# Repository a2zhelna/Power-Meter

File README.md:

# Power-Meter Rundown

### Anthony Zhelnakov

Demo video: https://www.dropbox.com/s/2afd6wcfme4bhvw/PowerMeterDemo.mp4?dl=0

This is a DC power meter, which utilizes an ESP32 to host an access point, which a user on a browser can connect to and view real-time data from. It utilizes FreeRTOS to make use of the ESP32’s dual core architecture for reading and uploading data in parallel.

The inner 16-bit ADC chip (ADS8331), responsible for making all of the measurements, is capable of making 500k samples per second, but for the graphical data-visualisation method I am using and simplicity of the program, I found that maxing out at about 1k samples per second worked and looked just fine (the task scheduler of the ESP32 runs 1000 times a second, so I corresponded it to that).

This device was inteded to be used for analyzing realtime changes in power consumption: the user can analyze what happens during power-on/off cycles, sleep modes, different hardware modes, what happens when certain peripherals are turned on and off, which is all very helpful for diagnosing issues or just testing.

---

### Sockets:

**PS+:**
The power supply’s — which powers the unit — positive terminal’s voltage. The recommended maximum with reference to PS- is 23V. 

**PS-:**
The power supply’s negative terminal’s voltage (GND).

**Unit+:**
The positive supply terminal of the load / unit being tested.

**High Current In:**
The negative supply terminal of the load / unit being tested, IF it draws from 0 - 7.5A.

**Low Current In:**
The negative supply terminal of the load / unit being tested, IF it draws from 0 - 20mA (uses a 250mA fuse).3

---

### Instructions:

1. Connect power supply to PS+ and PS-, and connect the unit under test to UNIT+ and an appropriate CURRENT IN socket.
2. Turn on the power meter device.
3. Connect via Wi-Fi to the ESP32’s access point “Power Meter”. Password is “password”. 
4. Go to “192.168.77.77” in a browser.
5. You should be directed to the website. If the readings are nonsensically high or aren’t updating, turn off the device and go back to step 2!
6. Click the start button before considering any of the readings.
7. Turn on the power supply and unit that is being tested.
8. Measure POWER!!!
9. If the current surpasses 7.5A, the unit will be disconnected, and the reset/start button will need to be pressed again.

---

### Protection:

If the current through the HIGH input exceeds 7.5A, a relay disconnects the input from the current measurement circuit and in turn from GND. This current threshold can be adjusted with the potentiometer. Also, if the µC somehow detects this excessive current, a warning is shown on the website.

The LOW current input is protected with a 250mA fuse. Additionally, if the current exceeds 20mA through the low current input, then a warning is shown on the website. The reason being is because at higher currents, the ammeter circuit acts unpredictably and gives garbage results that shouldn’t be interpreted. If there’s a warning, it is recommended to restart the measurement, preferably with the higher current range. 
Note that this overcurrent notification method isn’t full proof, since it relies on the sampling rate of the device. If the current goes from <20mA to >20mA within the current re-sampling time, then the device will determine if there’s an overcurrent with garbage data, and possibly not display the warning.

One of the ADC inputs is connected to the HIGH current input to measure burden voltage. If this input gets connected to a large voltage, there’s a resistor and a clamping diode set up to prevent the ADC’s input from going above 5.1V. Due to the burden voltage always being below 1V, this doesn’t add any significant inaccuracies. 

---

### ADC inputs:

**Power supply voltage:**
Measures the voltage across PS+ and PS-. This is done through a voltage divider, which divides the input by 6. Due to the ADC having a reference voltage of 4.096V, the maximum input that can be measured is (4.096V x 6) = 24.576V. The absolute maximum input is (5.3V x 6) = 31.8V.

**High current measurement:**
Meant for measuring current going INTO the “High Current In” socket. This current goes through the L18P003D15 9A hall effect current sensor, who’s output also goes to a voltage divider which divides it by 3, for ADC safety.

**Low current measurement:**
Meant for measuring current going INTO the “Low Current In” socket. This current goes through an op amp circuit called a “feedback ammeter”, which itself has virtually no burden voltage. It is only effective for currents less than 20mA. The output goes directly to the ADC input.

**Offset/burden voltage:** 
Measures the voltage at the “High Current In” socket. This socket connects to an 8A power relay (used for protection), which routes the current through the hall effect current sensor, which then routes the current directly to the power supply’s ground (PS- socket). This configuration results in a ~100mOhm load. For higher currents, that results in a significant burden.
This measured burden voltage is then subtracted from the measured power supply voltage.
Note: This reveals a minor design flaw. The low current measurement circuit’s burden voltage (which mainly results from the fuse) is not measured. Though, it is almost insignificant.

---

### “Instantaneous Power”

The PS voltage, low-current, high-current, and offset/burden voltage measurements (which are utilized together to calculate “instantaneous” power) are each ~55us apart, respectively (5us PGA delay + 40us other delay).

---

### Power Supply

This device has its own power supply which connects to the main 115VAC outlet. Utilizing a transformer, linear regulators and buck converter, it provides 5V and 3.3V for digital circuits, and a separate 5V, -5Va, 15Va and -15Va for analog circuits. The main reason for this is to have access to low-noise analog supply voltages, so that the output of the hall effect current sensor is clean and the ADC makes measurements as accurately as possible.

Both the power supply and the power meter PCBs utilize inductors to minimize noise on the analog line due to the digital line. The ESP32 µC sometimes requires a lot of current (upwards of 240mA), and supplying this using a linear regulator is not efficient and requires a large heatsink + constant airflow. I instead used a buck converter for this purpose, who’s output produces noise on the digital line which is “filtered” by these inductors.

---

### Accuracy

The power meter device was compared to (and calibrated with) the FLUKE 77IV Multimeter. The measurements/readings from the power supply (PS) are also listed below.

To summarize, there’s virtually always a <1% magnitude deviation from the FLUKE measurements with low current above 3mA, high current above 100mA, and voltage measurements above 300mV. See tables below for exact comparisons.

> Current at 20mA range setting

> Current at 7.5A range setting

> Voltage (No Load)

> Voltage (at UNIT+ and HIGH CURRENT IN sockets) with 1Ohm Load

---

### Voltage Burden

For the low current measurement circuit, the highest possible voltage drop across it is insignificant, due to the low current it's meant for.

For the high current measurement circuit however, there’s about 100mOhms from the overcurrent relay and hall effect sensor, and there’s about 45mOhms from the wires connecting the unit’s sockets to the actual power meter PCB. To give an idea on the effect this has, at 7.5A, it results in a ~1V drop across those elements. 
The ADC actually measures the burden across the relay and hall effect, but as for the wires’ burden, an estimation is calculated. These voltages are then subtracted from the measured power supply voltage to give the voltage across the sockets that the unit connects to. On top of that, there’s an option to specify resistance of the leads that connect to the unit. Using the measured current, more voltage burden is calculated and subtracted from the power supply voltage 

**It is thus imperative** for the user to look at the voltage displayed on the website to make evaluations on the unit’s power consumption, instead of using the value displayed on their power supply. 
(But the user must be careful with the custom lead resistance option as entering a high resistance will significantly drop the voltage shown on the website, providing the user with a skewed view on how much they can increase the power supply voltage — which can lead to the ADC being damaged). 

Burden voltage is also the justification for the recommended 23V PS input limit. As an example, let's say the user’s unit under test is drawing 7.5A of current. This means that the voltage across the mentioned-before elements of the measurement device is around 1V. Thus, the voltage across the unit is 1V less than the voltage from the PS. If the user applies the maximum measurable voltage, 24.5V, at the PS inputs, then the website will display 23.5V. If the user knows they can measure up to 24.5V, they might think they can increase the PS voltage after it has already oversaturated the ADC input, which will lend inaccurate results. 
So, for the device to be reliable in this edge case, it is recommended to apply a maximum voltage of 23V at the unit’s terminals.

---

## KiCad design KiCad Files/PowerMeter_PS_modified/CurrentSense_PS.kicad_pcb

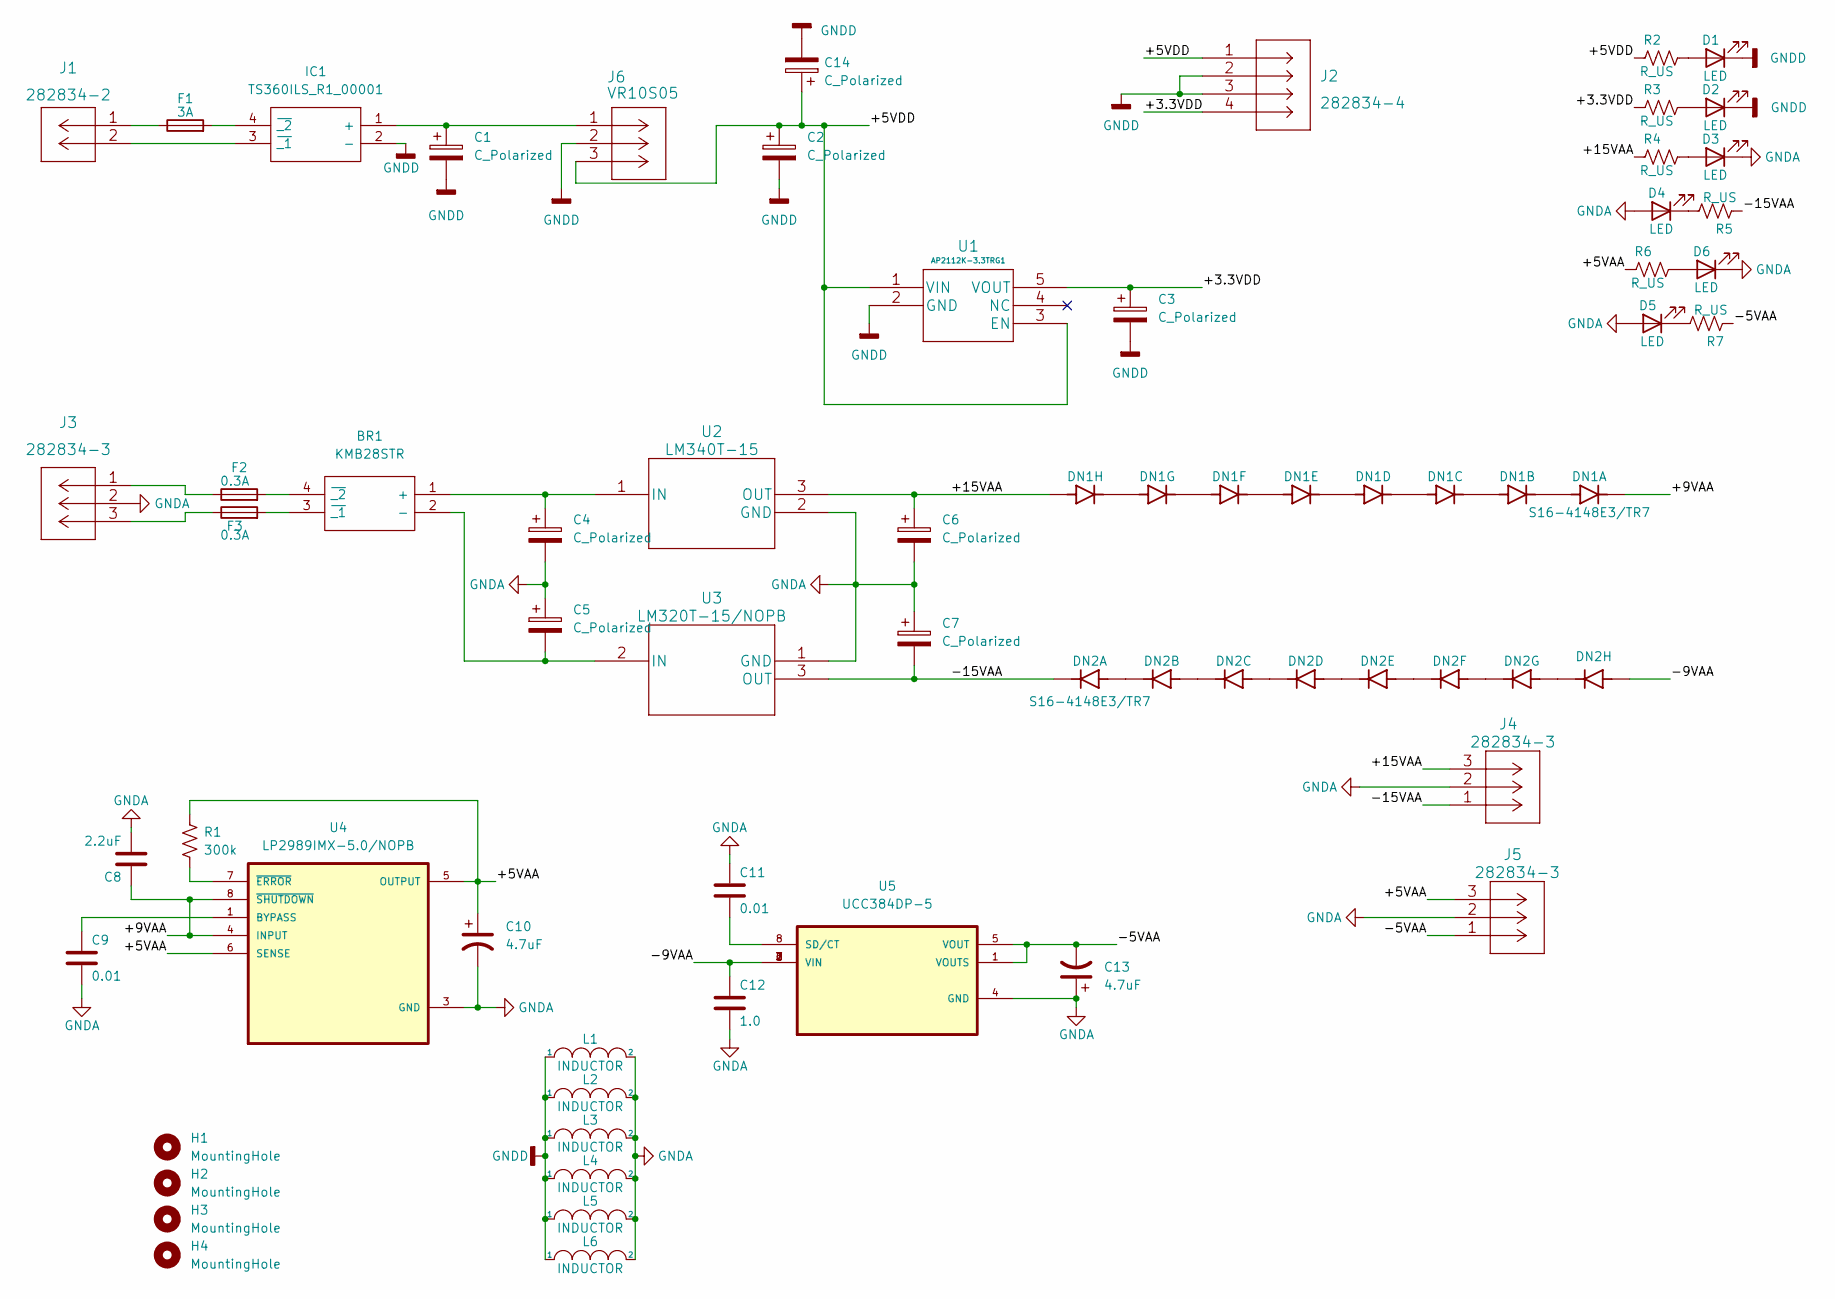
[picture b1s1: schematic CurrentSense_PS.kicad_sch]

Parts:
BR1: KMB28STR; SOP250P700X290-4N; Manufacturer_Part_Number KMB28STR
C1, C2, C3, C4, C5, C6, C7, C14: C_Polarized; CP_Radial_D5.0mm_P2.50mm
C8: 2.2uF; C_0805_2012Metric
C9, C11: 0.01; C_0603_1608Metric
C10, C13: 4.7uF; CP_EIA-7343-15_Kemet-W
C12: 1.0; C_0603_1608Metric
D1, D2, D3, D4, D5, D6: LED; LED_0603_1608Metric
DN1, DN2: S16-4148E3/TR7; SOIC127P599X195-16N; PARTREV G
F1: 3A; Fuse_1206_3216Metric
F2, F3: 0.3A; Fuse_1206_3216Metric
H1, H2, H3, H4: MountingHole; MountingHole_3.2mm_M3
IC1: TS360ILS_R1_00001; SOP400P650X145-4N; Mouser Part Number 241-TS360ILSR100001
J1: 282834-2
J2: 282834-4
J3, J4, J5: 282834-3
J6: VR10S05
L1, L2, L3, L4, L5, L6: INDUCTOR; L_1206_3216Metric
R1: 300k; R_0603_1608Metric
R2, R3, R4, R5, R6, R7: R_US; R_0603_1608Metric
U1: AP2112K-3.3TRG1
U2: LM340T-15
U3: LM320T-15/NOPB; LM320T-15&slash_NOPB
U4: LP2989IMX-5.0/NOPB; SOIC127P599X175-8N
U5: UCC384DP-5; SOIC127P599X175-8N

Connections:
/+3.3VDD: C3.1, J2.4, R3.1, U1.5 (VOUT)
/+5VAA: C10.1, J5.3, R1.1, R6.1, U4.5 (OUTPUT), U4.6 (SENSE)
/+5VDD: C2.1, C14.1, J2.1, J6.3, R2.1, U1.1 (VIN), U1.3 (EN)
/+9VAA: C8.1, DN1.1, U4.4 (INPUT), U4.8 (~SHUTDOWN)
/+15VAA: C6.1, DN1.9, J4.3, R4.1, U2.3 (OUT)
/-5VAA: C13.2, J5.1, R7.1, U5.1 (VOUTS), U5.5 (VOUT)
/-9VAA: C12.1, DN2.9, U5.2 (VIN), U5.3 (VIN), U5.6 (VIN), U5.7 (VIN)
/-15VAA: C7.2, DN2.1, J4.1, R5.1, U3.3 (OUT)
GNDA: C4.2, C5.1, C6.2, C7.1, C8.2, C9.2, C10.2, C11.1, C12.2, C13.1, D3.1 (K), D4.2 (A), D5.2 (A), D6.1 (K), J3.2, J4.2, J5.2, L1.2, L2.2, L3.2, L4.2, L5.2, L6.2, U2.2 (GND), U3.1 (GND), U4.3 (GND), U5.4 (GND)
GNDD: C1.2, C2.2, C3.2, C14.2, D1.1 (K), D2.1 (K), IC1.2 (-), J2.2, J2.3, J6.2, L1.1, L2.1, L3.1, L4.1, L5.1, L6.1, U1.2 (GND)
unnamed: BR1.1 (+), C4.1, U2.1 (IN)
unnamed: BR1.2 (-), C5.2, U3.2 (IN)
unnamed: BR1.3 (~_1), F3.2
unnamed: BR1.4 (~_2), F2.2
unnamed: C1.1, IC1.1 (+), J6.1
unnamed: C9.1, U4.1 (BYPASS)
unnamed: C11.2, U5.8 (SD/CT)
unnamed: D1.2 (A), R2.2
unnamed: D2.2 (A), R3.2
unnamed: D3.2 (A), R4.2
unnamed: D4.1 (K), R5.2
unnamed: D5.1 (K), R7.2
unnamed: D6.2 (A), R6.2
unnamed: DN1.8, DN1.10
unnamed: DN1.7, DN1.11
unnamed: DN1.6, DN1.12
unnamed: DN1.5, DN1.13
unnamed: DN1.4, DN1.14
unnamed: DN1.3, DN1.15
unnamed: DN1.2, DN1.16
unnamed: DN2.8, DN2.10
unnamed: DN2.7, DN2.11
unnamed: DN2.6, DN2.12
unnamed: DN2.5, DN2.13
unnamed: DN2.4, DN2.14
unnamed: DN2.3, DN2.15
unnamed: DN2.2, DN2.16
unnamed: F1.1, J1.1
unnamed: F1.2, IC1.4 (~_2)
unnamed: F2.1, J3.1
unnamed: F3.1, J3.3
unnamed: IC1.3 (~_1), J1.2
unnamed: R1.2, U4.7 (~ERROR)

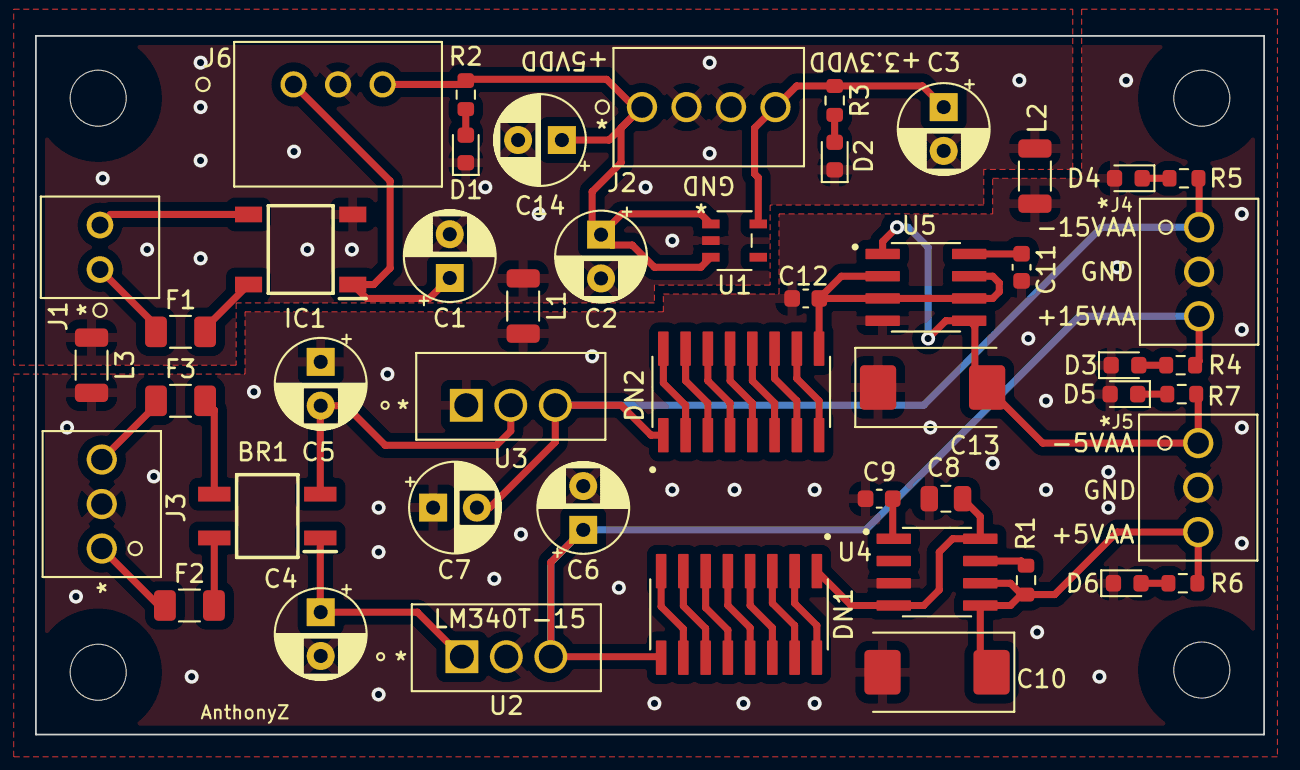
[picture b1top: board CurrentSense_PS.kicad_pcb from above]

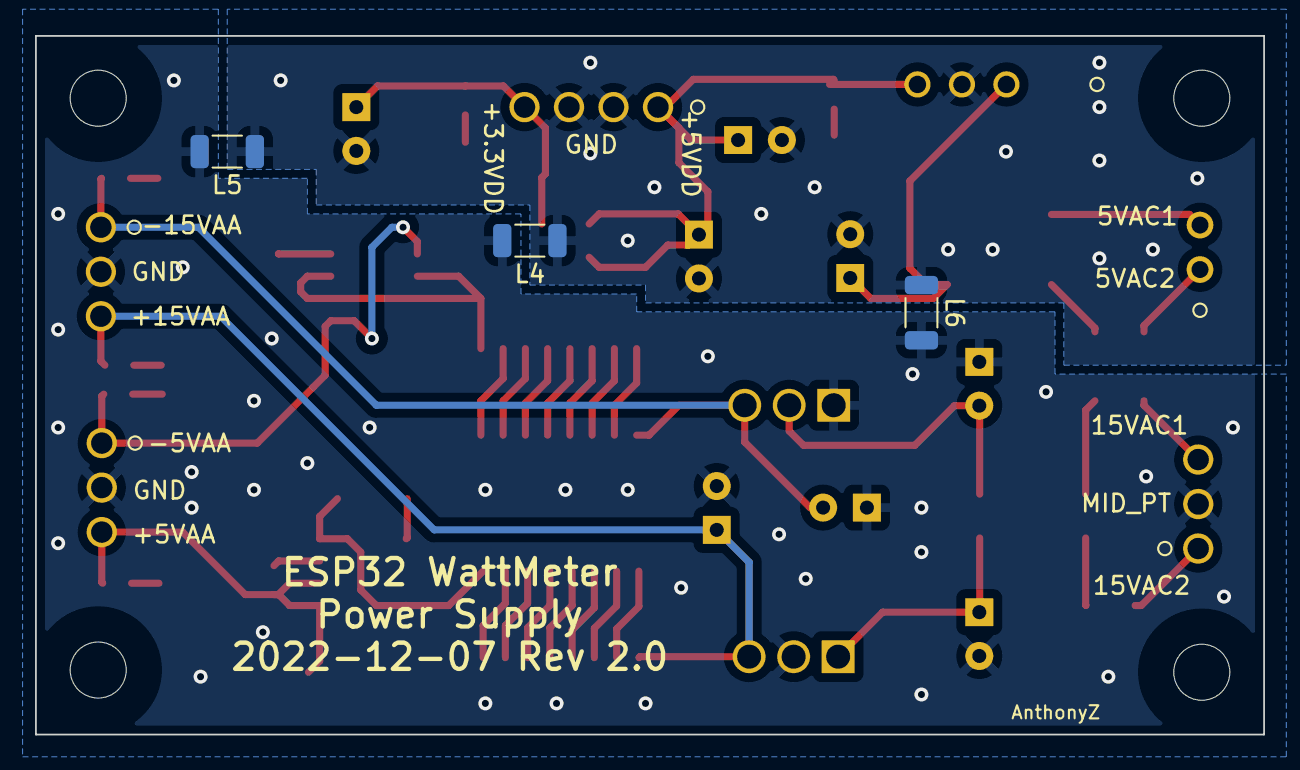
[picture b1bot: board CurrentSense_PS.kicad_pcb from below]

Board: 2 copper layers, 70.1 x 39.9 mm, 55 parts (3 on the bottom side), 43 nets.

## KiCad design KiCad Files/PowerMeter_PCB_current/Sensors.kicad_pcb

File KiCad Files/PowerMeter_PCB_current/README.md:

# Voltage-Current-Sense-Circuit

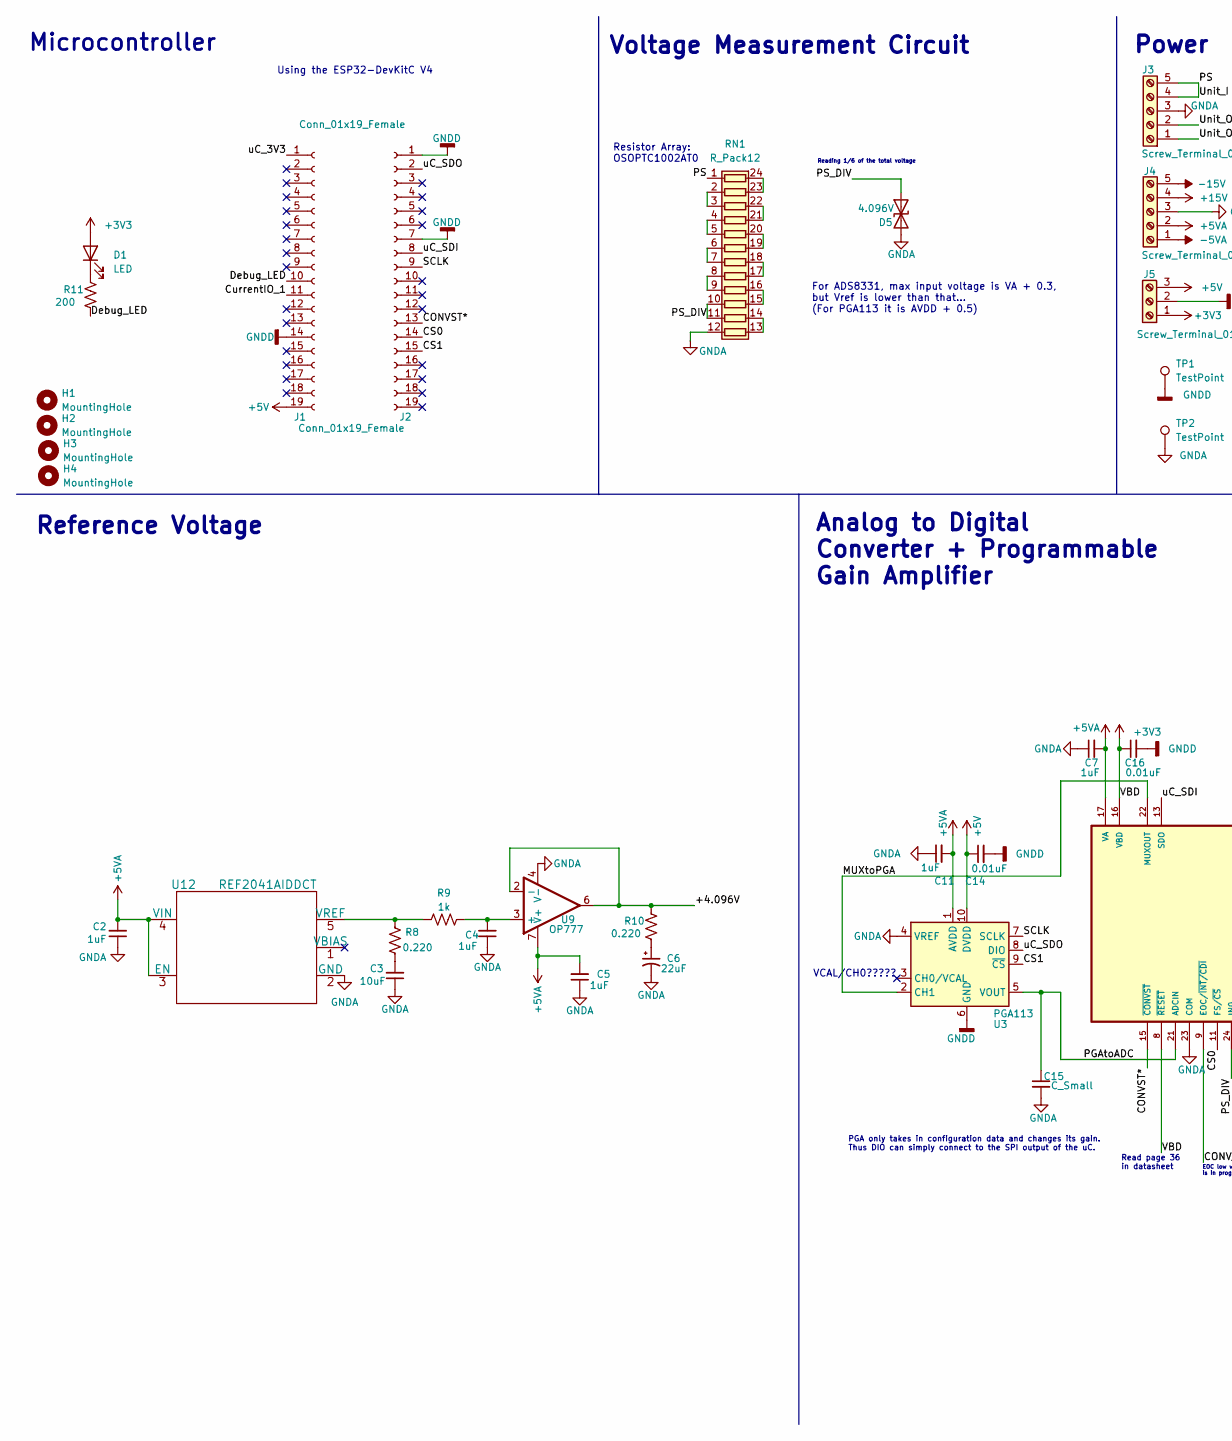
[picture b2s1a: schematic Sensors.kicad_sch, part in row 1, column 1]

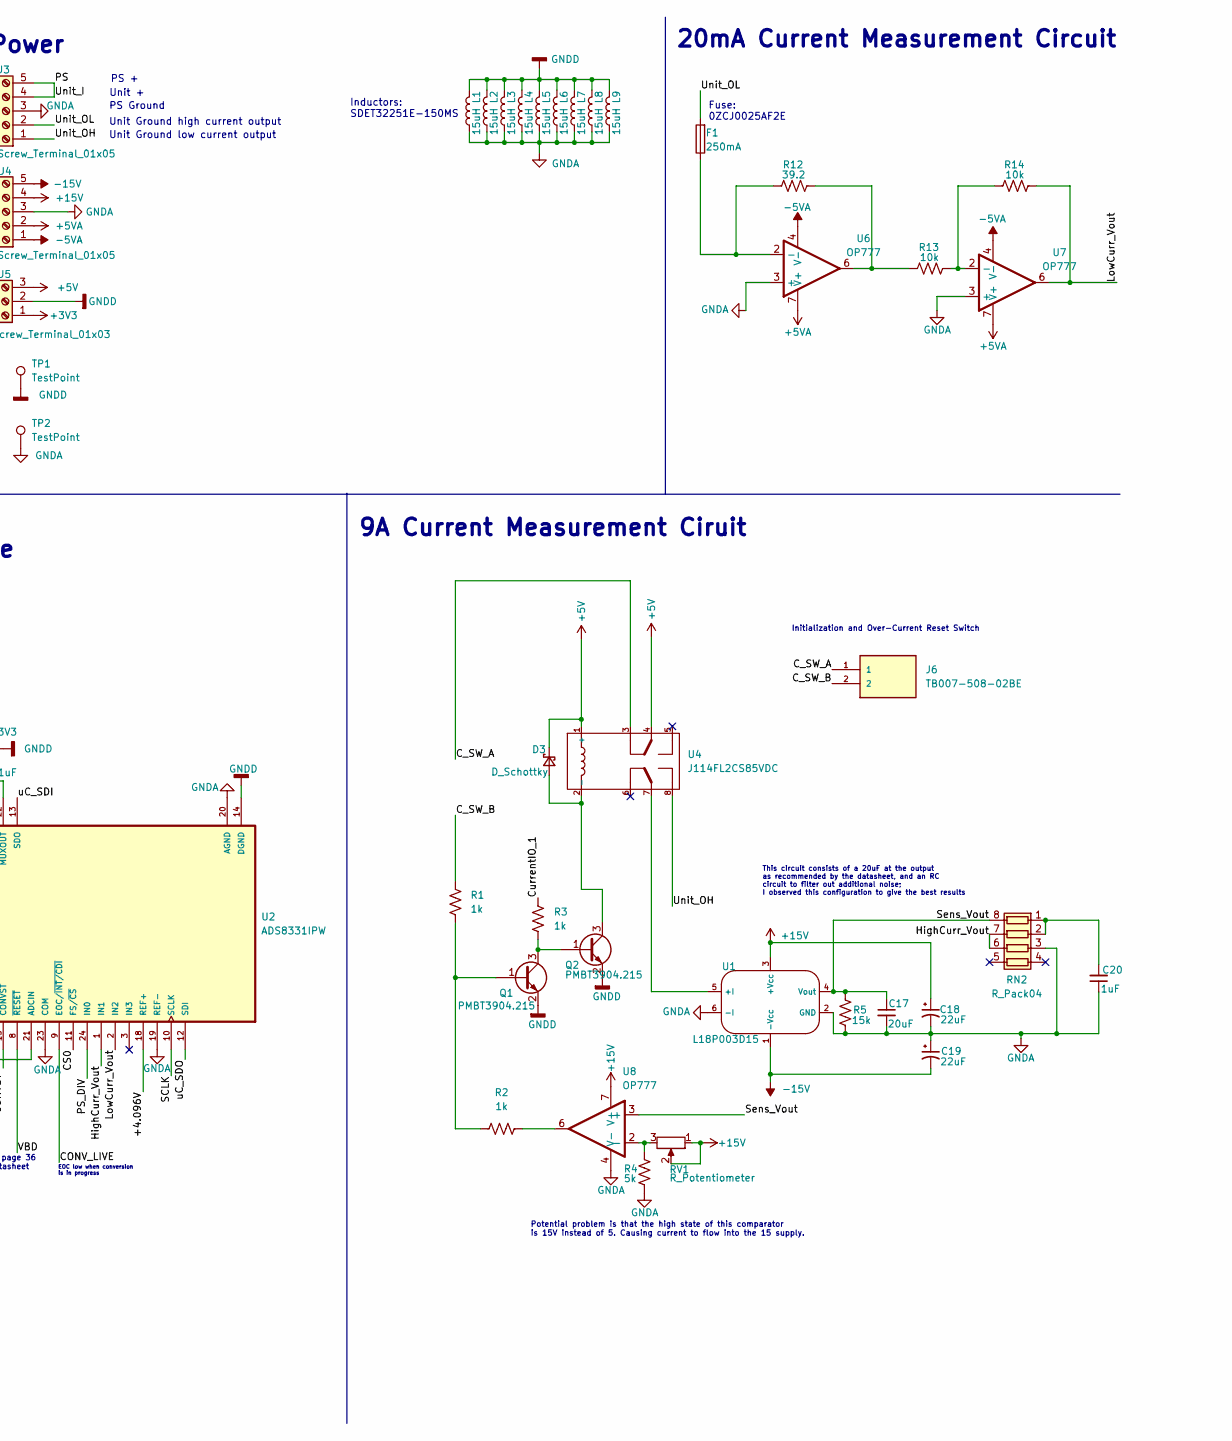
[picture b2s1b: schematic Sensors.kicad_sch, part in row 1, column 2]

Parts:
C2, C4, C5, C7, C11, C20: 1uF; C_0603_1608Metric
C3: 10uF; C_0603_1608Metric
C6, C18, C19: 22uF; 293D226X9020D8T
C14, C16: 0.01uF; C_0603_1608Metric
C15: C_Small; C_0603_1608Metric
C17: 20uF; C_0603_1608Metric
D1: LED; LED_0603_1608Metric
D3: D_Schottky; SOT91P240X102-3N
D5: 4.096V; D_1206_3216Metric
F1: 250mA; Fuse_1206_3216Metric
H1, H2, H3, H4: MountingHole; MountingHole_3.2mm_M3
J1, J2: Conn_01x19_Female; PinSocket_1x19_P2.54mm_Vertical
J3, J4: Screw_Terminal_01x05; CUI_TB007-508-05BE
J5: Screw_Terminal_01x03; TB007-508-03BE
J6: TB007-508-02BE; CUI_TB007-508-02BE
L1, L2, L3, L4, L5, L6, L7, L8, L9: 15uH; SDET32251E-150MS
Q1, Q2: PMBT3904.215; TSOT-23
R1, R2, R3, R9: 1k; R_0603_1608Metric
R4: 5k; R_0603_1608Metric
R5: 15k; R_0603_1608Metric
R8, R10: 0.220; R_0603_1608Metric
R11: 200; R_0603_1608Metric
R12: 39.2; R_0603_1608Metric
R13, R14: 10k; R_0603_1608Metric
RN1: R_Pack12; SSOP-24_3.9x8.7mm_P0.635mm
RN2: R_Pack04; ACASA1002S1002P1AT
RV1: R_Potentiometer; Potentiometer_Bourns_3296W_Vertical
TP1, TP2: TestPoint; TestPoint_THTPad_1.5x1.5mm_Drill0.7mm
U1: L18P003D15
U2: ADS8331IPW; SOP65P640X120-24N
U3: PGA113; TSSOP-10_3x3mm_P0.5mm
U4: J114FL2CS85VDC
U6, U7, U8, U9: OP777; TSSOP-8_3x3mm_P0.65mm
U12: REF2041AIDDCT

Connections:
+3V3: C16.1, D1.2 (A), J5.1, U2.8 (~RESET), U2.16 (VBD)
+5V: C14.1, D3.1 (K), J1.19, J5.3, U3.10 (DVDD), U4.1 (+), U4.4
+5VA: C2.2, C5.2, C7.2, C11.2, J4.2, U2.17 (VA), U3.1 (AVDD), U6.7 (V+), U7.7 (V+), U9.7 (V+), U12.3 (EN), U12.4 (VIN)
+15V: C18.1, J4.4, RV1.1, RV1.2, U1.3 (+Vcc), U8.7 (V+)
-5VA: J4.1, U6.4 (V-), U7.4 (V-)
-15V: C19.2, J4.5, U1.1 (-Vcc)
/+4.096V: R10.1, U2.18 (REF+), U9.2 (-), U9.6
/CONVST*: J2.13, U2.15 (~CONVST)
/CONV_LIVE: U2.9 (EOC/~INT/CDI)
/CS0: J2.14, U2.11 (FS/~CS)
/CS1: J2.15, U3.9 (~CS)
/C_SW_A: J6.1, U4.3
/C_SW_B: J6.2, R1.2
/CurrentIO_1: J1.11, R3.1
/Debug_LED: J1.10, R11.2
/HighCurr_Vout: RN2.6 (R3.2), RN2.7 (R2.2), U2.1 (IN1)
/LowCurr_Vout: R14.1, U2.2 (IN2), U7.6
/MUXtoPGA: U2.22 (MUXOUT), U3.2 (CH1)
/PGAtoADC: C15.1, U2.21 (ADCIN), U3.5 (VOUT)
/PS: J3.4, J3.5, RN1.1 (R1.1)
/PS_DIV: D5.1 (A1), RN1.10 (R10.1), RN1.11 (R11.1), U2.24 (IN0)
/SCLK: J2.9, U2.10 (SCLK), U3.7 (SCLK)
/Sens_Vout: C17.1, R5.2, RN2.8 (R1.2), U1.4 (Vout), U8.3 (+)
/Unit_OH: J3.1, U4.8
/Unit_OL: F1.2, J3.2
/uC_3V3: J1.1
/uC_SDI: J2.8, U2.13 (SDO)
/uC_SDO: J2.2, U2.12 (SDI), U3.8 (DIO)
GNDA: C2.1, C3.1, C4.1, C5.1, C6.2, C7.1, C11.1, C15.2, C17.2, C18.2, C19.1, C20.1, D5.2 (A2), J3.3, J4.3, L1.1, L2.1, L3.1, L4.1, L5.1, L6.1, L7.1, L8.1, L9.1, R4.1, R5.1, RN1.12 (R12.1), RN2.3 (R3.1), TP2.1, U1.2 (GND), U1.6 (-I), U2.19 (REF-), U2.20 (AGND), U2.23 (COM), U3.4 (VREF), U6.3 (+), U7.3 (+), U8.4 (V-), U9.4 (V-), U12.2 (GND)
GNDD: C14.2, C16.2, J1.14, J2.1, J2.7, J5.2, L1.2, L2.2, L3.2, L4.2, L5.2, L6.2, L7.2, L8.2, L9.2, Q1.2 (E), Q2.2 (E), TP1.1, U2.14 (DGND), U3.6 (GND)
unnamed: C3.2, R8.1
unnamed: C4.2, R9.1, U9.3 (+)
unnamed: C6.1, R10.2
unnamed: C20.2, RN2.1 (R1.1), RN2.2 (R2.1)
unnamed: D1.1 (K), R11.1
unnamed: D3.2 (A), Q2.3 (C), U4.2 (-)
unnamed: F1.1, R12.2, U6.2 (-)
unnamed: Q1.1 (B), R1.1, R2.1
unnamed: Q1.3 (C), Q2.1 (B), R3.2
unnamed: R2.2, U8.6
unnamed: R4.2, RV1.3, U8.2 (-)
unnamed: R8.2, R9.2, U12.5 (VREF)
unnamed: R12.1, R13.2, U6.6
unnamed: R13.1, R14.2, U7.2 (-)
unnamed: RN1.2 (R2.1), RN1.3 (R3.1)
unnamed: RN1.4 (R4.1), RN1.5 (R5.1)
unnamed: RN1.6 (R6.1), RN1.7 (R7.1)
unnamed: RN1.8 (R8.1), RN1.9 (R9.1)
unnamed: RN1.13 (R12.2), RN1.14 (R11.2)
unnamed: RN1.15 (R10.2), RN1.16 (R9.2)
unnamed: RN1.17 (R8.2), RN1.18 (R7.2)
unnamed: RN1.19 (R6.2), RN1.20 (R5.2)
unnamed: RN1.21 (R4.2), RN1.22 (R3.2)
unnamed: RN1.23 (R2.2), RN1.24 (R1.2)
unnamed: U1.5 (+I), U4.7

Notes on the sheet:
Potential problem is that the high state of this comparator is 15V instead of 5. Causing current to flow into the 15 supply.
20mA Current Measurement Circuit
Unit +
For ADS8331, max input voltage is VA + 0.3, but Vref is lower than that... (For PGA113 it is AVDD + 0.5)
PS +
Power
Unit Ground low current output
Reference Voltage
Resistor Array: OSOPTC1002AT0
Using the ESP32-DevKitC V4
Microcontroller
This circuit consists of a 20uF at the output as recommended by the datasheet, and an RC circuit to filter out additional noise; I observed this configuration to give the best results
EOC low when conversion is in progress
PS Ground
Initialization and Over-Current Reset Switch
PGA only takes in configuration data and changes its gain. Thus DIO can simply connect to the SPI output of the uC.
Fuse: 0ZCJ0025AF2E
Read page 36 in datasheet
VCAL/CH0?????
Voltage Measurement Circuit
Inductors: SDET32251E-150MS
Analog to Digital Converter + Programmable Gain Amplifier
9A Current Measurement Ciruit
Reading 1/6 of the total voltage
Unit Ground high current output

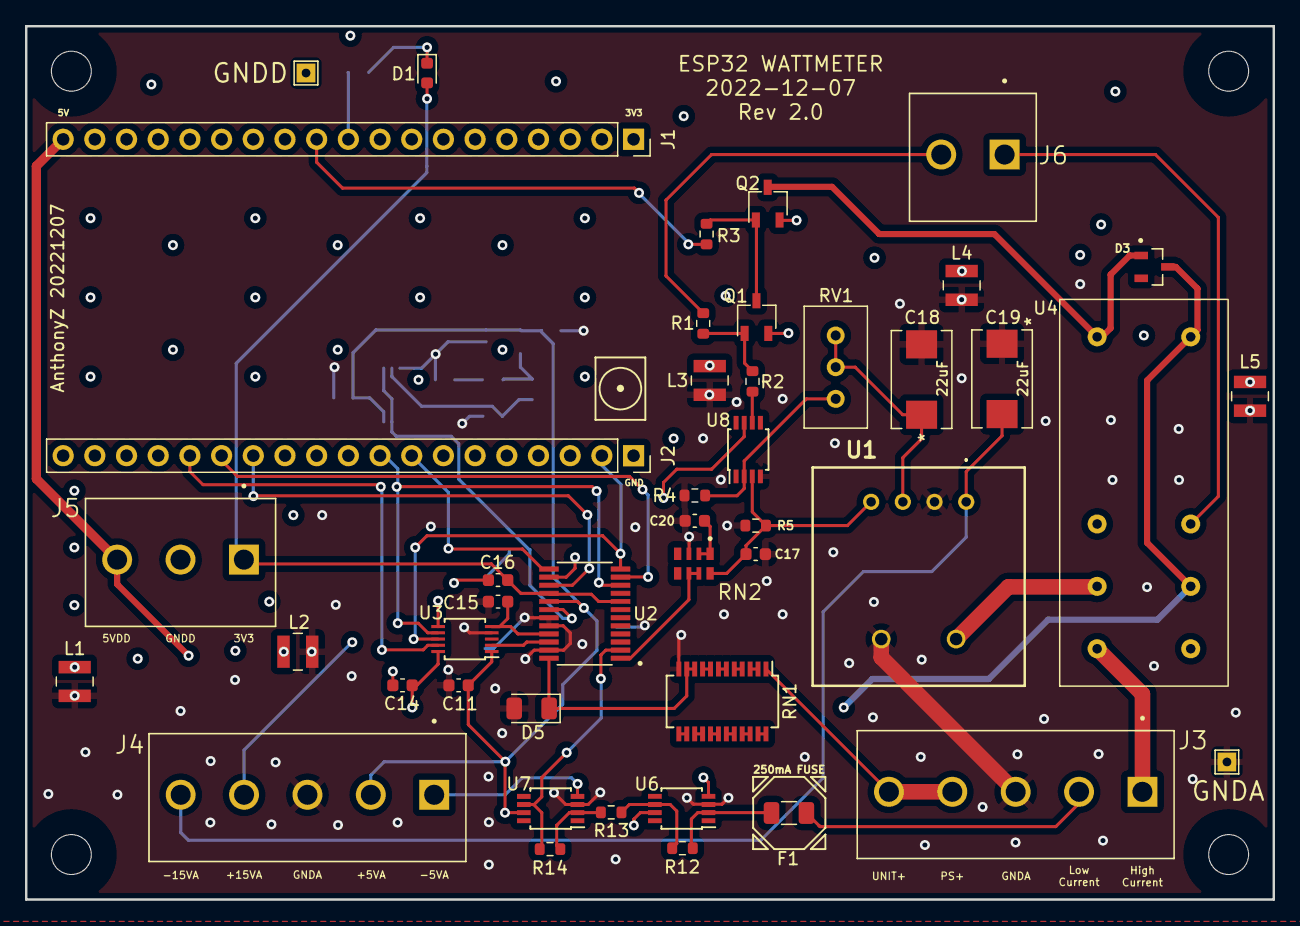
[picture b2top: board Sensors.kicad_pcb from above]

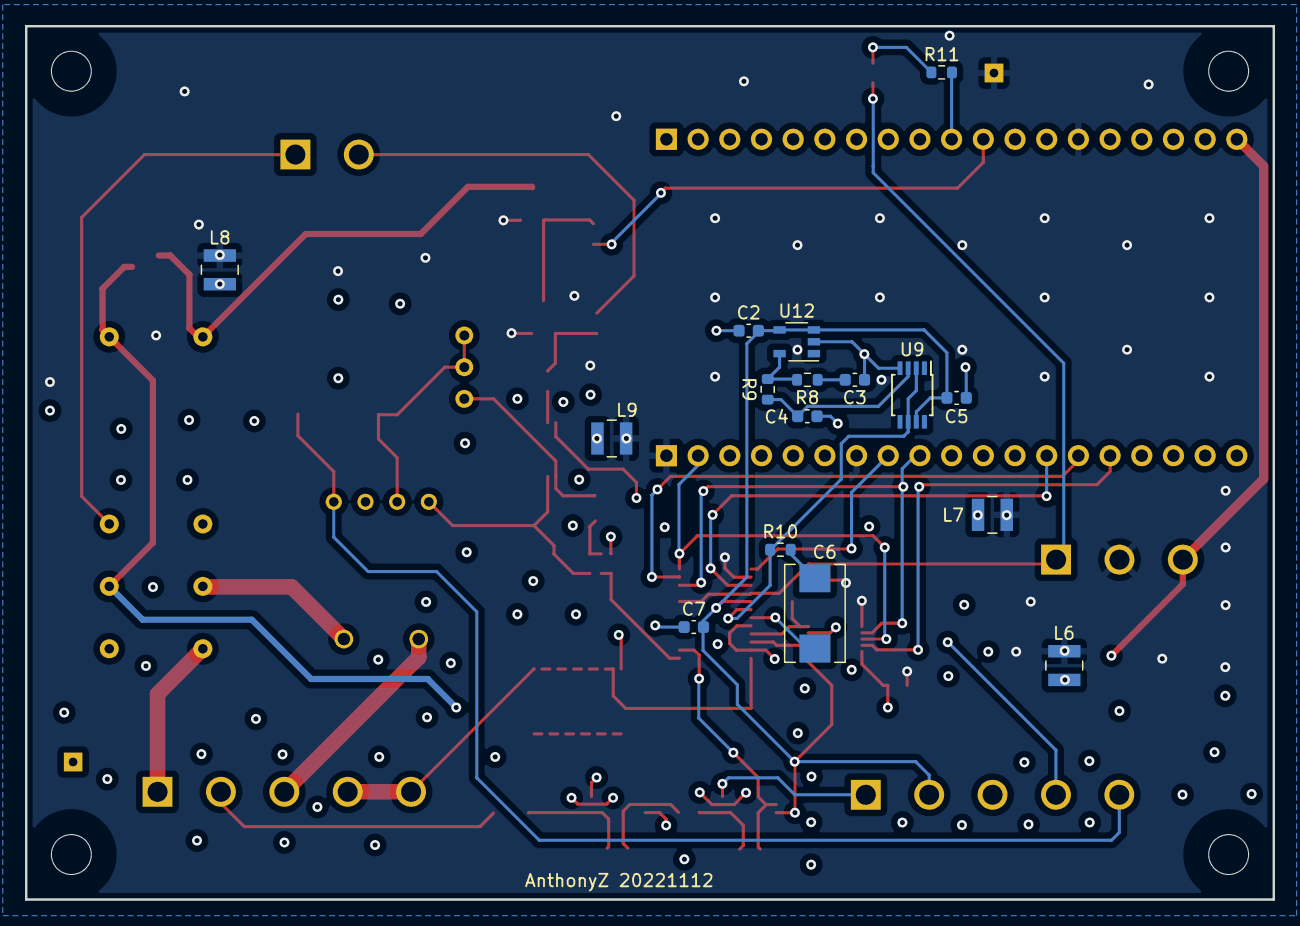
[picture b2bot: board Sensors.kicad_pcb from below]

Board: 4 copper layers, 100.0 x 70.0 mm, 65 parts (16 on the bottom side), 53 nets.

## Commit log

2023-01-08 Committing all project files
2023-01-09 Adding video demo link.

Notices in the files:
parts and their libraries:
Copyright 2021 Accelerated Designs. All rights reserved.
